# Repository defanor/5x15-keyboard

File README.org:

* A 5x15 keyboard
This is a keyboard project. That's also my first hardware project, so
in case if somebody would want to reuse it, be careful. Though I've
built it and it works.

The keyboard has 5 rows and 15 columns (well, depends on how one
counts, but approximately that much), and intended to be handy for
emacs: has plenty of accessible modifier keys, and never requires to
get too far from the home row.

More information, photos, and the build process description can be
found in the "[[https://defanor.uberspace.net/notes/building-a-keyboard.xhtml][building a keyboard]]" note.

** Dependencies and software
The switches are borrowed from [[https://www.ergodox.io/][ergodox]] (and altered a bit), and the
[[https://github.com/LuisDiazUgena/Teensy-3.1][LuisDiazUgena/Teensy-3.1]] library for kicad is used. KiCad and LibreCAD
were used, by the way.

For the firmware, I've used PaulStoffregen/{[[https://github.com/PaulStoffregen/cores][cores]],
[[https://github.com/PaulStoffregen/teensy_loader_cli][teensy_loader_cli]]}. Changes introduced to ~teensy3/Makefile~:

#+BEGIN_EXAMPLE
 # configurable options
-OPTIONS = -DF_CPU=48000000 -DUSB_SERIAL -DLAYOUT_US_ENGLISH -DUSING_MAKEFILE
+OPTIONS = -DF_CPU=48000000 -DUSB_KEYBOARDONLY -DLAYOUT_US_ENGLISH -DUSING_MAKEFILE
#+END_EXAMPLE

Then it can be built with ~NO_ARDUINO=1 make~.

** License
Hopefully without violating licenses of the reused bits, this project
is GPL-licensed.

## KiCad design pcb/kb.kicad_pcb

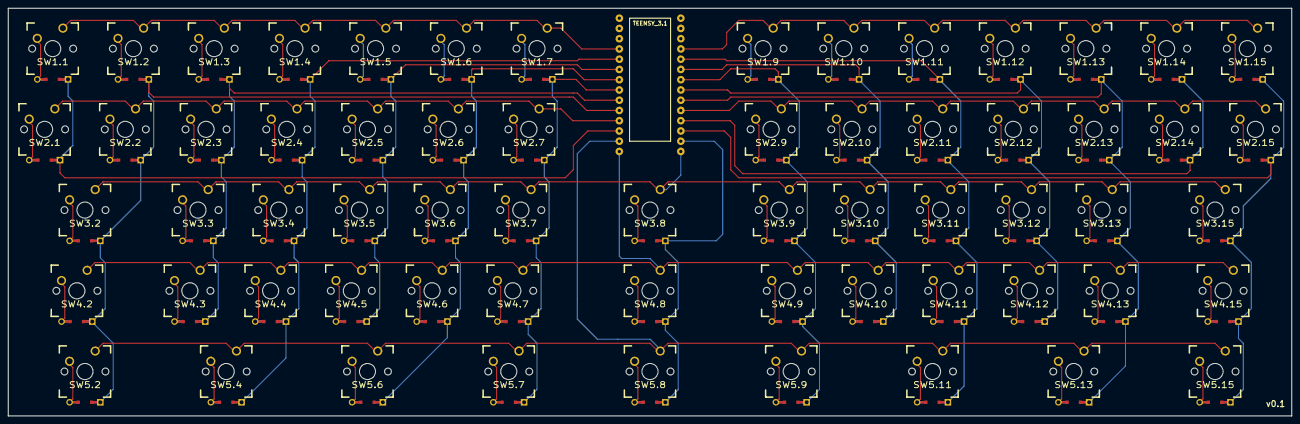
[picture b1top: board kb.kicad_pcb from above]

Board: 2 copper layers, 318.0 x 101.0 mm, 64 parts (0 on the bottom side), 85 nets.

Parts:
SW1.1, SW1.2, SW1.3, SW1.4, SW1.5, SW1.6, SW1.7, SW1.9, SW1.10, SW1.11, SW1.12, SW1.13, SW1.14, SW1.15, SW2.1, SW2.2, SW2.3, SW2.4, SW2.5, SW2.6, SW2.7, SW2.9, SW2.10, SW2.11, SW2.12, SW2.13, SW2.14, SW2.15, SW3.3, SW3.4, SW3.5, SW3.6, SW3.7, SW3.9, SW3.10, SW3.11, SW3.12, SW3.13, SW4.3, SW4.4, SW4.5, SW4.6, SW4.7, SW4.9, SW4.10, SW4.11, SW4.12, SW4.13: SWITCH_DIODE; MX_FLIP_DIODE
SW3.2, SW3.8, SW3.15, SW4.2, SW4.8, SW4.15, SW5.2, SW5.4, SW5.6, SW5.7, SW5.8, SW5.9, SW5.11, SW5.13, SW5.15: SWITCH_DIODE; MX_FLIP_DIODE_1_75
U1: TEENSY_3.1

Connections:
/col-1: SW1.1.4, SW2.1.4, U1.10
/col-2: SW1.2.4, SW2.2.4, SW3.2.4, SW4.2.4, SW5.2.4, U1.8
/col-3: SW1.3.4, SW2.3.4, SW3.3.4, SW4.3.4, U1.7
/col-4: SW1.4.4, SW2.4.4, SW3.4.4, SW4.4.4, SW5.4.4, U1.3
/col-5: SW1.5.4, SW2.5.4, SW3.5.4, SW4.5.4, U1.4
/col-6: SW1.6.4, SW2.6.4, SW3.6.4, SW4.6.4, SW5.6.4, U1.5
/col-7: SW1.7.4, SW2.7.4, SW3.7.4, SW4.7.4, SW5.7.4, U1.6
/col-8: SW3.8.4, SW4.8.4, SW5.8.4, U1.14
/col-9: SW1.9.4, SW2.9.4, SW3.9.4, SW4.9.4, SW5.9.4, U1.20
/col-10: SW1.10.4, SW2.10.4, SW3.10.4, SW4.10.4, U1.21
/col-11: SW1.11.4, SW2.11.4, SW3.11.4, SW4.11.4, SW5.11.4, U1.22
/col-12: SW1.12.4, SW2.12.4, SW3.12.4, SW4.12.4, U1.19
/col-13: SW1.13.4, SW2.13.4, SW3.13.4, SW4.13.4, SW5.13.4, U1.18
/col-14: SW1.14.4, SW2.14.4, U1.16
/col-15: SW1.15.4, SW2.15.4, SW3.15.4, SW4.15.4, SW5.15.4, U1.15
/row-1-left: SW1.1.1, SW1.2.1, SW1.3.1, SW1.4.1, SW1.5.1, SW1.6.1, SW1.7.1, U1.2
/row-1-right: SW1.9.1, SW1.10.1, SW1.11.1, SW1.12.1, SW1.13.1, SW1.14.1, SW1.15.1, U1.23
/row-2-left: SW2.1.1, SW2.2.1, SW2.3.1, SW2.4.1, SW2.5.1, SW2.6.1, SW2.7.1, U1.9
/row-2-right: SW2.9.1, SW2.10.1, SW2.11.1, SW2.12.1, SW2.13.1, SW2.14.1, SW2.15.1, U1.17
/row-3: SW3.2.1, SW3.3.1, SW3.4.1, SW3.5.1, SW3.6.1, SW3.7.1, SW3.8.1, SW3.9.1, SW3.10.1, SW3.11.1, SW3.12.1, SW3.13.1, SW3.15.1, U1.13
/row-4: SW4.2.1, SW4.3.1, SW4.4.1, SW4.5.1, SW4.6.1, SW4.7.1, SW4.8.1, SW4.9.1, SW4.10.1, SW4.11.1, SW4.12.1, SW4.13.1, SW4.15.1, U1.12
/row-5: SW5.2.1, SW5.4.1, SW5.6.1, SW5.7.1, SW5.8.1, SW5.9.1, SW5.11.1, SW5.13.1, SW5.15.1, U1.11
unnamed: SW1.9.2, SW1.9.3
unnamed: SW2.9.2, SW2.9.3
unnamed: SW3.9.2, SW3.9.3
unnamed: SW4.9.2, SW4.9.3
unnamed: SW5.9.2, SW5.9.3
unnamed: SW3.8.2, SW3.8.3
unnamed: SW4.8.2, SW4.8.3
unnamed: SW5.8.2, SW5.8.3
unnamed: SW4.11.2, SW4.11.3
unnamed: SW3.10.2, SW3.10.3
unnamed: SW2.10.2, SW2.10.3
unnamed: SW1.10.2, SW1.10.3
unnamed: SW1.11.2, SW1.11.3
unnamed: SW2.11.2, SW2.11.3
unnamed: SW3.11.2, SW3.11.3
unnamed: SW4.10.2, SW4.10.3
unnamed: SW5.11.2, SW5.11.3
unnamed: SW1.5.2, SW1.5.3
unnamed: SW2.5.2, SW2.5.3
unnamed: SW3.5.2, SW3.5.3
unnamed: SW4.5.2, SW4.5.3
unnamed: SW1.6.2, SW1.6.3
unnamed: SW2.6.2, SW2.6.3
unnamed: SW3.6.2, SW3.6.3
unnamed: SW3.4.2, SW3.4.3
unnamed: SW1.4.2, SW1.4.3
unnamed: SW2.4.2, SW2.4.3
unnamed: SW4.4.2, SW4.4.3
unnamed: SW5.4.2, SW5.4.3
unnamed: SW1.7.2, SW1.7.3
unnamed: SW2.7.2, SW2.7.3
unnamed: SW3.7.2, SW3.7.3
unnamed: SW4.7.2, SW4.7.3
unnamed: SW5.7.2, SW5.7.3
unnamed: SW4.6.2, SW4.6.3
unnamed: SW5.6.2, SW5.6.3
unnamed: SW4.15.2, SW4.15.3
unnamed: SW5.15.2, SW5.15.3
unnamed: SW5.13.2, SW5.13.3
unnamed: SW5.2.2, SW5.2.3
unnamed: SW3.12.2, SW3.12.3
unnamed: SW4.12.2, SW4.12.3
unnamed: SW2.12.2, SW2.12.3
unnamed: SW1.12.2, SW1.12.3
unnamed: SW1.14.2, SW1.14.3
unnamed: SW1.15.2, SW1.15.3
unnamed: SW2.15.2, SW2.15.3
unnamed: SW1.13.2, SW1.13.3
unnamed: SW2.13.2, SW2.13.3
unnamed: SW3.13.2, SW3.13.3
unnamed: SW4.13.2, SW4.13.3
unnamed: SW3.15.2, SW3.15.3
unnamed: SW2.14.2, SW2.14.3
unnamed: SW4.2.2, SW4.2.3
unnamed: SW2.2.2, SW2.2.3
unnamed: SW3.3.2, SW3.3.3
unnamed: SW4.3.2, SW4.3.3
unnamed: SW1.1.2, SW1.1.3
unnamed: SW1.2.2, SW1.2.3
unnamed: SW1.3.2, SW1.3.3
unnamed: SW2.1.2, SW2.1.3
unnamed: SW3.2.2, SW3.2.3
unnamed: SW2.3.2, SW2.3.3

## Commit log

2017-01-21 Fix the ergodox link
2021-01-23 Update a hyperlink
